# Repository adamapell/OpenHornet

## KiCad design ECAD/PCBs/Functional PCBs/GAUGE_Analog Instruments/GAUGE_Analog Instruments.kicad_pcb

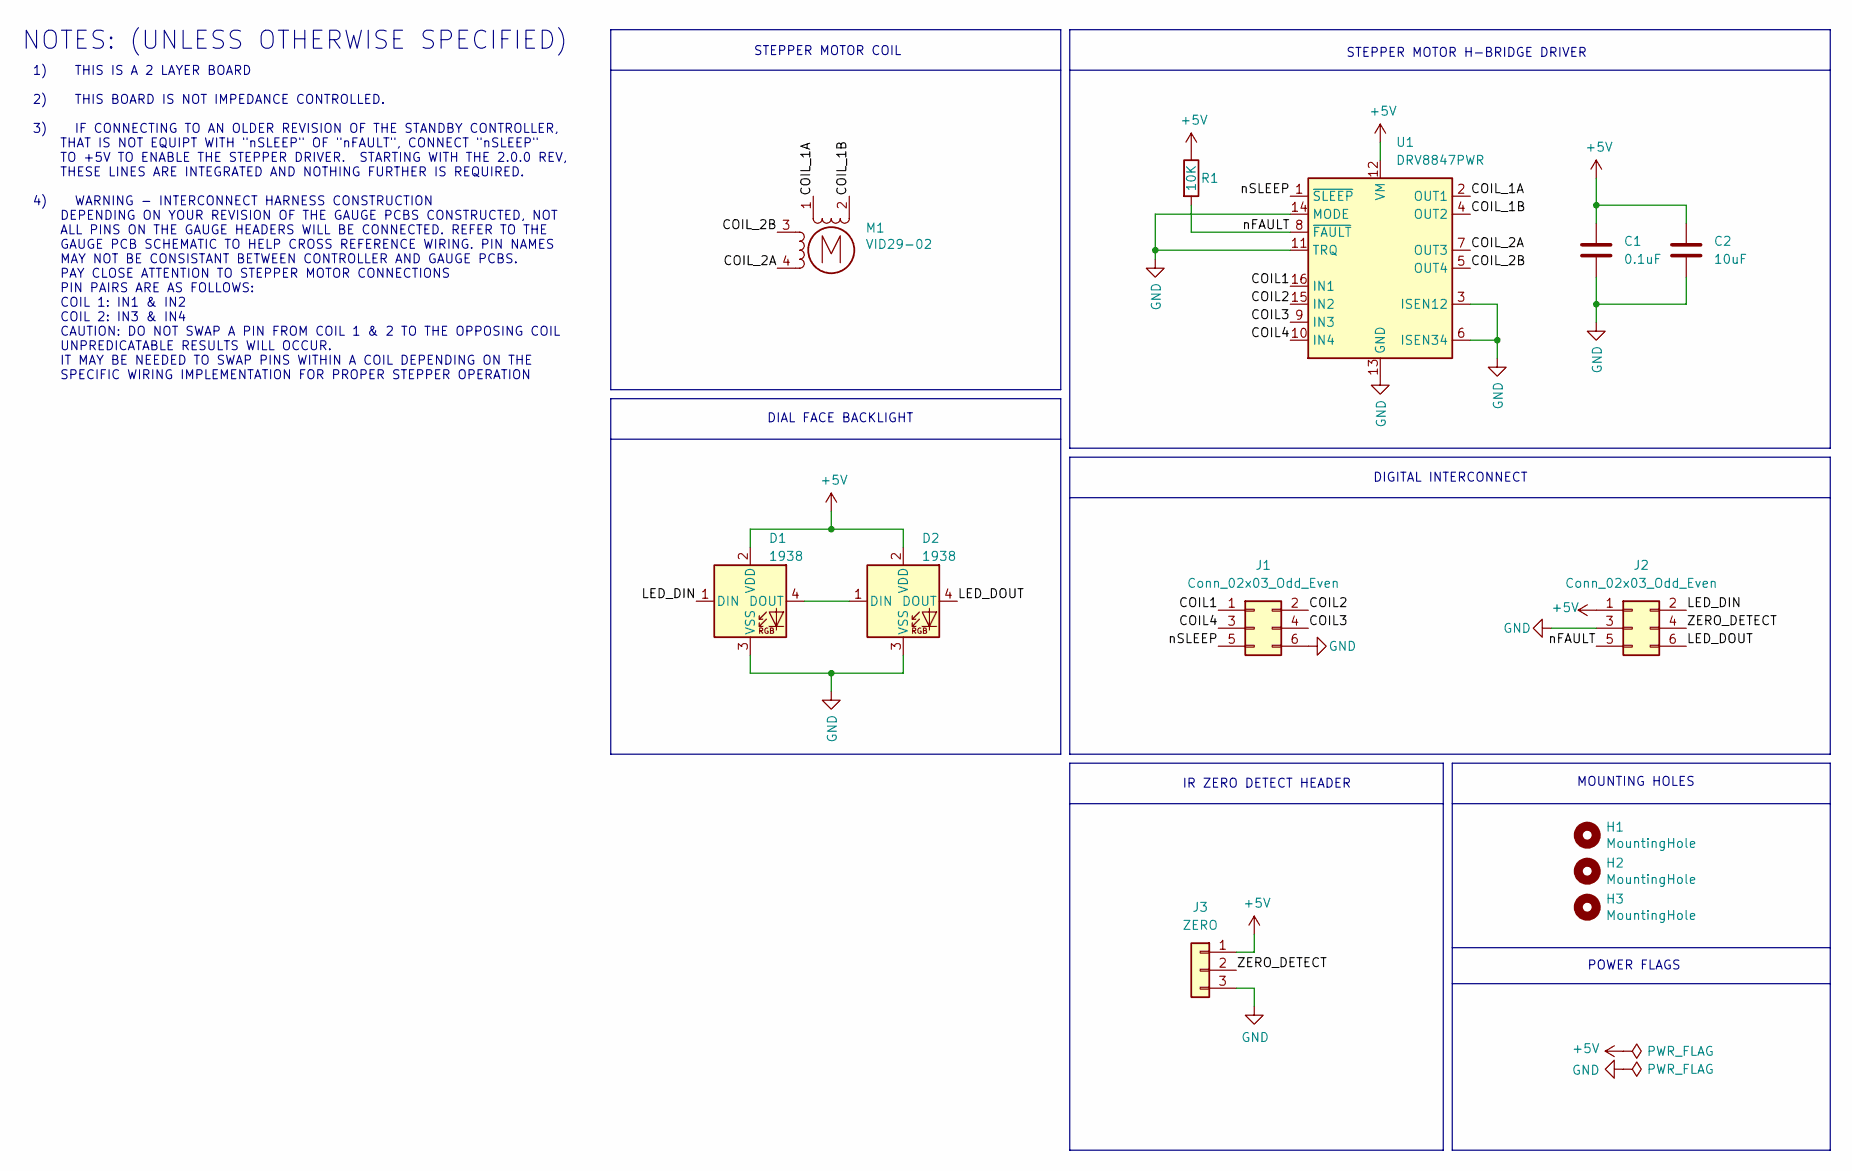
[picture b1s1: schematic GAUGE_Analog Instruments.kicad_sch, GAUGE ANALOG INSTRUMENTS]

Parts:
C1: 0.1uF; C_0603_1608Metric; Manufacturer PN CC0603KRX7R9BB104; LCSC C14663
C2: 10uF; C_0603_1608Metric; Manufacturer PN CL10A106MA8NRNC; LCSC C96446
D1, D2: 1938; LED_D5.0mm-4_RGB
H1, H2, H3: MountingHole; MountingHole_2.5mm
J1, J2: Conn_02x03_Odd_Even; PinHeader_2x03_P2.54mm_Vertical
J3: ZERO; PinHeader_1x03_P2.54mm_Vertical; Manufacturer PN PH1-03-UA
M1: VID29-02
R1: 10K; R_0603_1608Metric; LCSC C25804
U1: DRV8847PWR; TSSOP-16_4.4x5mm_P0.65mm; LCSC C701803

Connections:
+5V: C1.1, C2.1, D1.2 (VDD), D2.2 (VDD), J2.1, J3.1, R1.1, U1.12 (VM)
/COIL1: J1.1, U1.16 (IN1)
/COIL2: J1.2, U1.15 (IN2)
/COIL3: J1.4, U1.9 (IN3)
/COIL4: J1.3, U1.10 (IN4)
/COIL_1A: M1.1, U1.2 (OUT1)
/COIL_1B: M1.2 (-_2), U1.4 (OUT2)
/COIL_2A: M1.4, U1.7 (OUT3)
/COIL_2B: M1.3, U1.5 (OUT4)
/LED_DIN: D1.1 (DIN), J2.2
/LED_DOUT: D2.4 (DOUT), J2.6
/ZERO_DETECT: J2.4, J3.2
/nFAULT: J2.5, R1.2, U1.8 (~FAULT)
/nSLEEP: J1.5, U1.1 (~SLEEP)
GND: C1.2, C2.2, D1.3 (VSS), D2.3 (VSS), J1.6, J2.3, J3.3, U1.3 (ISEN12), U1.6 (ISEN34), U1.11 (TRQ), U1.13 (GND), U1.14 (MODE)
unnamed: D1.4 (DOUT), D2.1 (DIN)

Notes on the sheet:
STEPPER MOTOR COIL
IR ZERO DETECT HEADER
POWER FLAGS
DIAL FACE BACKLIGHT
DIGITAL INTERCONNECT
MOUNTING HOLES
1) THIS IS A 2 LAYER BOARD 2) THIS BOARD IS NOT IMPEDANCE CONTROLLED. 3) IF CONNECTING TO AN OLDER REVISION OF THE STANDBY CONTROLLER, THAT IS NOT EQUIPT WITH "nSLEEP" OF "nFAULT", CONNECT "nSLEEP" TO +5V TO ENABLE THE STEPPER DRIVER. STARTING WITH THE 2.0.0 REV, THESE LINES ARE INTEGRATED AND NOTH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
NOTES: (UNLESS OTHERWISE SPECIFIED)
STEPPER MOTOR H-BRIDGE DRIVER

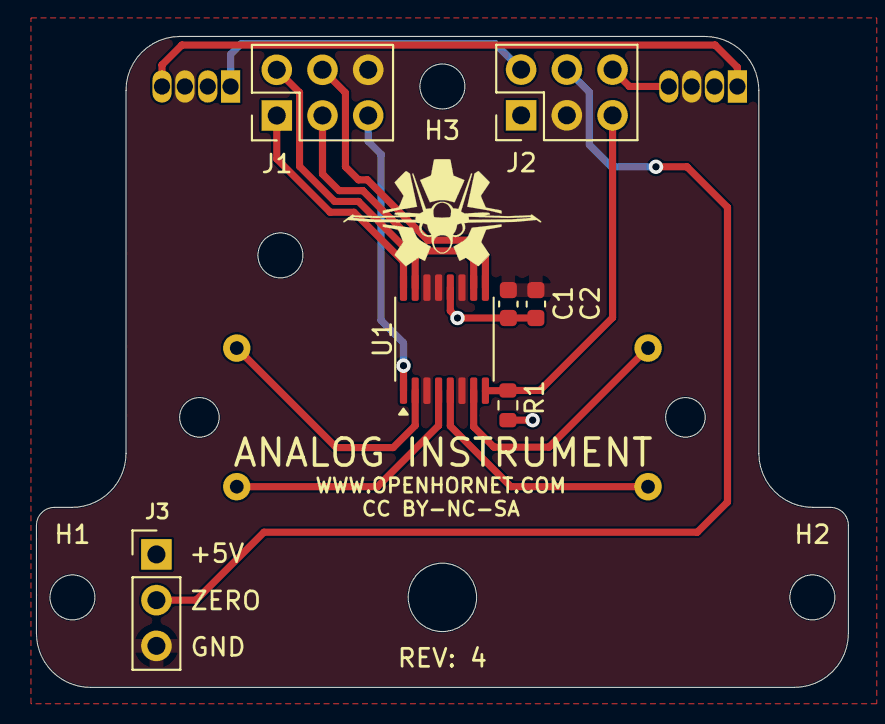
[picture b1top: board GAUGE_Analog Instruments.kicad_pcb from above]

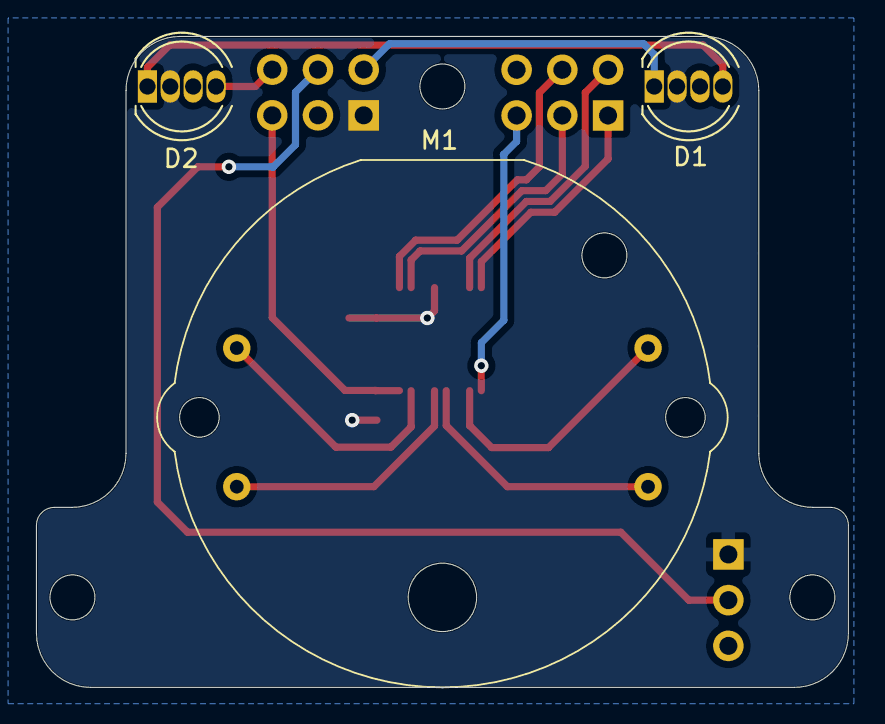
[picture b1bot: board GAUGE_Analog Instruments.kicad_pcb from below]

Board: 2 copper layers, 45.1 x 36.2 mm, 14 parts (2 on the bottom side), 16 nets.

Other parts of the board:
LOGO: LOGO; LOGO_OH_NoText_Small

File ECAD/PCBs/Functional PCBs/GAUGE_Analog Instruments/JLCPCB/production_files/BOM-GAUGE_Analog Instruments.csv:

Comment,Designator,Footprint,LCSC,Quantity
0.1uF,C1,C_0603_1608Metric,C14663,1
10K,R1,R_0603_1608Metric,C25804,1
10uF,C2,C_0603_1608Metric,C96446,1
DRV8847PWR,U1,TSSOP-16_4.4x5mm_P0.65mm,C701803,1
1938,D2,LED_D5.0mm-4_RGB,,1
1938,D1,LED_D5.0mm-4_RGB,,1
VID29-02,M1,VID29-02,,1
MountingHole,H3,MountingHole_2.5mm,,1
MountingHole,H2,MountingHole_2.5mm,,1
MountingHole,H1,MountingHole_2.5mm,,1
Conn_02x03_Odd_Even,J2,PinHeader_2x03_P2.54mm_Vertical,,1
Conn_02x03_Odd_Even,J1,PinHeader_2x03_P2.54mm_Vertical,,1
ZERO,J3,PinHeader_1x03_P2.54mm_Vertical,,1

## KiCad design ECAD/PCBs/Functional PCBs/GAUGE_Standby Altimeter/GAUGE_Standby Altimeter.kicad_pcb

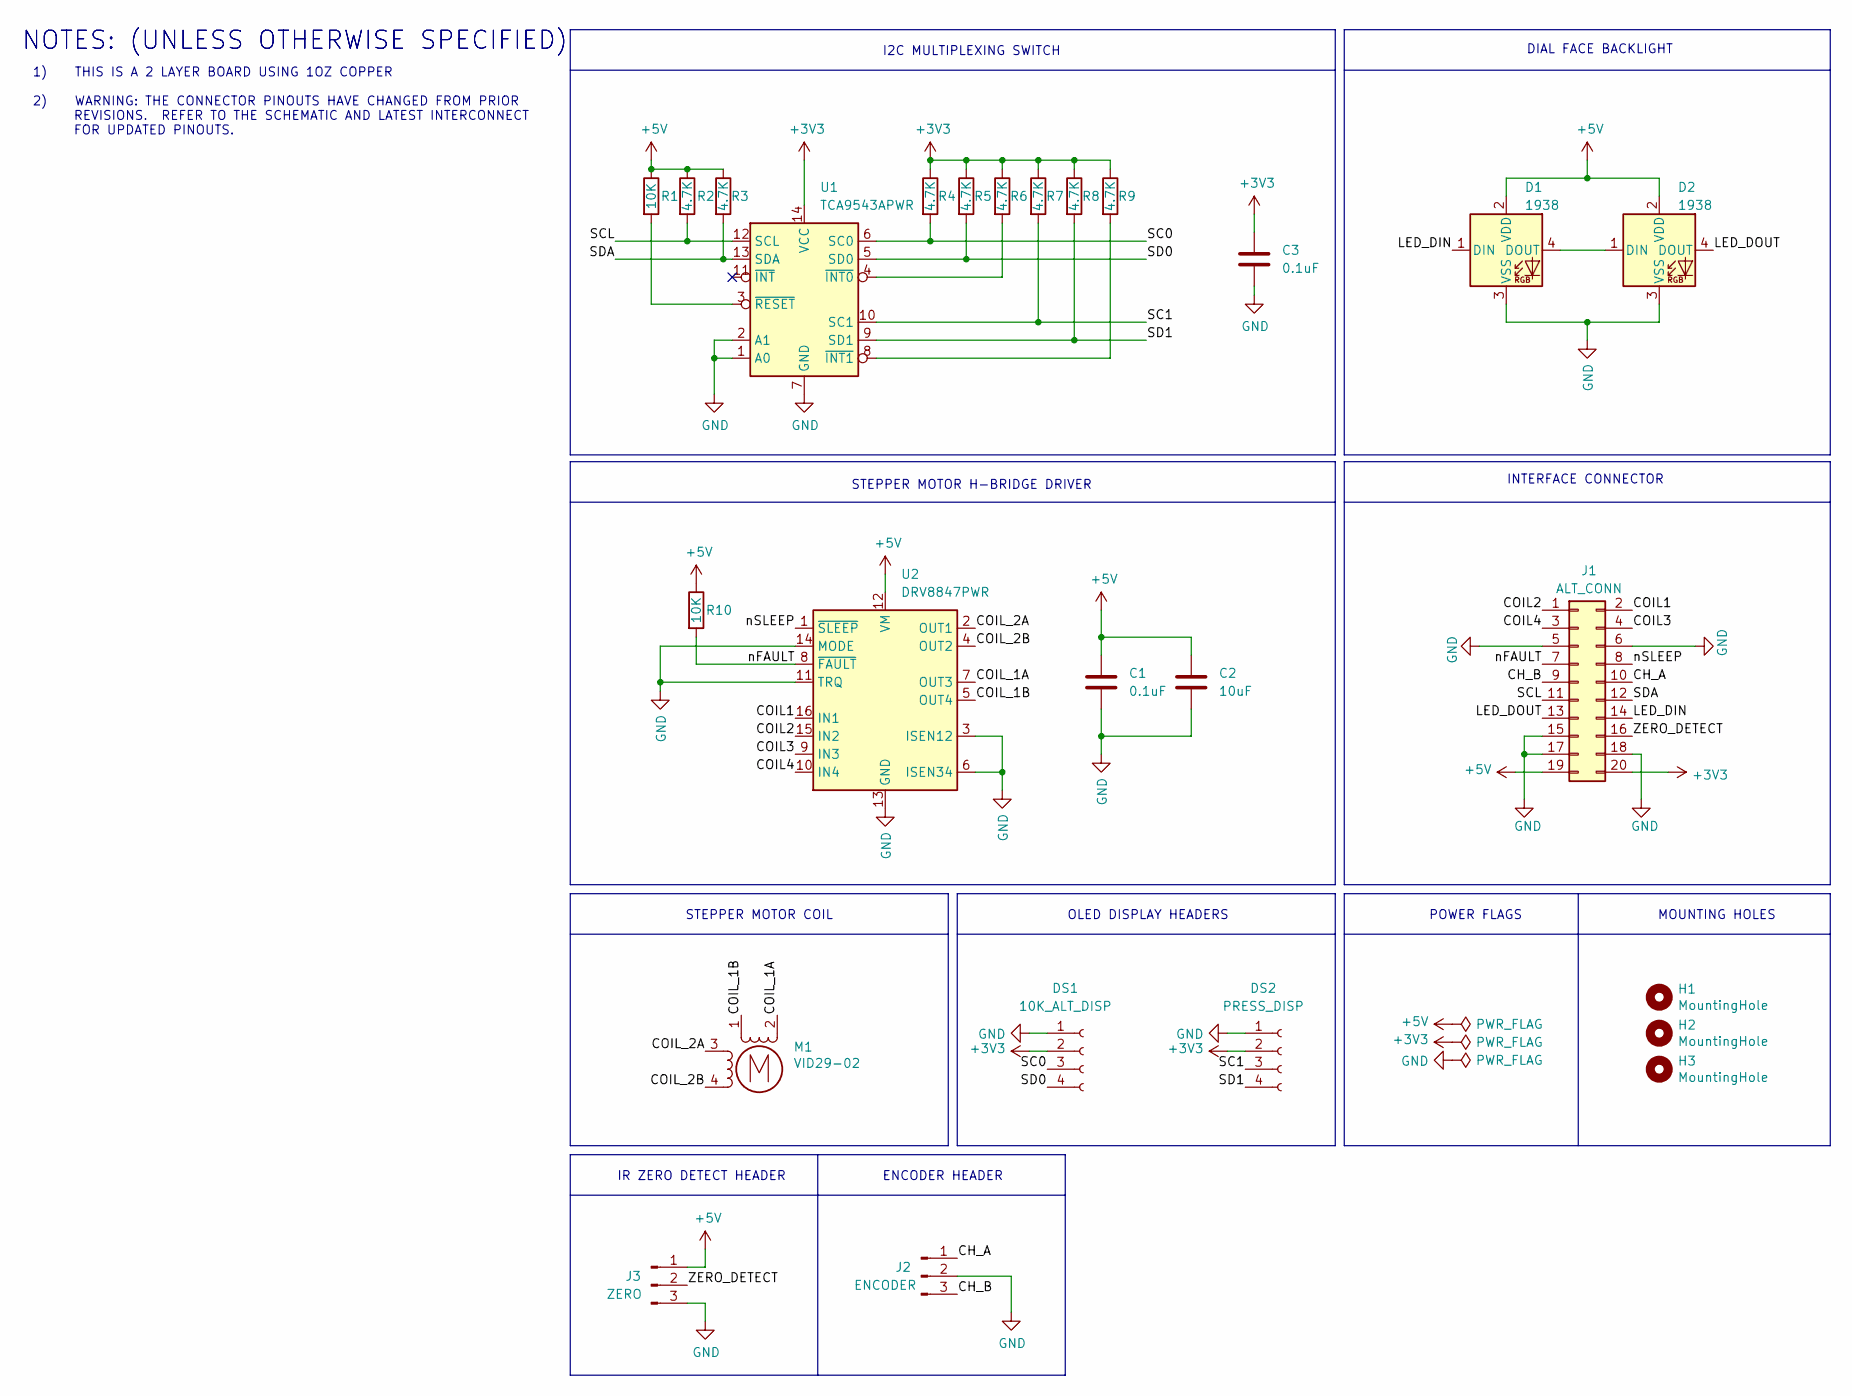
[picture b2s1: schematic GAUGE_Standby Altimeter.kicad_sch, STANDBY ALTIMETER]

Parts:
C1, C3: 0.1uF; C_0603_1608Metric; Manufacturer PN CC0603KRX7R9BB104; LCSC C14663
C2: 10uF; C_0603_1608Metric; Manufacturer PN CL10A106MA8NRNC; LCSC C96446
D1, D2: 1938; LED_D5.0mm-4_RGB
DS1: 10K_ALT_DISP; PinSocket_1x04_P2.54mm_Vertical
DS2: PRESS_DISP; PinSocket_1x04_P2.54mm_Vertical
H1, H2, H3: MountingHole; MountingHole_2.5mm
J1: ALT_CONN; PinHeader_2x10_P2.54mm_Vertical; Manufacturer PN PH2-10-UA
J2: ENCODER; PinHeader_1x03_P2.54mm_Vertical
J3: ZERO; PinHeader_1x03_P2.54mm_Vertical
M1: VID29-02
R1, R10: 10K; R_0603_1608Metric; LCSC C25804
R2, R3, R4, R5, R6, R7, R8, R9: 4.7K; R_0603_1608Metric; Manufacturer PN 0603WAF4701T5E; LCSC C23162
U1: TCA9543APWR; TSSOP-14_4.4x5mm_P0.65mm; LCSC C2653307
U2: DRV8847PWR; TSSOP-16_4.4x5mm_P0.65mm; LCSC C701803

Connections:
+3V3: C3.1, DS1.2, DS2.2, J1.20, R4.1, R5.1, R6.1, R7.1, R8.1, R9.1, U1.14 (VCC)
+5V: C1.1, C2.1, D1.2 (VDD), D2.2 (VDD), J1.19, J3.1, R1.1, R2.1, R3.1, R10.1, U2.12 (VM)
/CH_A: J1.10, J2.1
/CH_B: J1.9, J2.3
/COIL1: J1.2, U2.16 (IN1)
/COIL2: J1.1, U2.15 (IN2)
/COIL3: J1.4, U2.9 (IN3)
/COIL4: J1.3, U2.10 (IN4)
/COIL_1A: M1.2 (-_2), U2.7 (OUT3)
/COIL_1B: M1.1, U2.5 (OUT4)
/COIL_2A: M1.3, U2.2 (OUT1)
/COIL_2B: M1.4, U2.4 (OUT2)
/LED_DIN: D1.1 (DIN), J1.14
/LED_DOUT: D2.4 (DOUT), J1.13
/SC0: DS1.3, R4.2, U1.6 (SC0)
/SC1: DS2.3, R7.2, U1.10 (SC1)
/SCL: J1.11, R2.2, U1.12 (SCL)
/SD0: DS1.4, R5.2, U1.5 (SD0)
/SD1: DS2.4, R8.2, U1.9 (SD1)
/SDA: J1.12, R3.2, U1.13 (SDA)
/ZERO_DETECT: J1.16, J3.2
/nFAULT: J1.7, R10.2, U2.8 (~FAULT)
/nSLEEP: J1.8, U2.1 (~SLEEP)
GND: C1.2, C2.2, C3.2, D1.3 (VSS), D2.3 (VSS), DS1.1, DS2.1, J1.5, J1.6, J1.15, J1.17, J1.18, J2.2, J3.3, U1.1 (A0), U1.2 (A1), U1.7 (GND), U2.3 (ISEN12), U2.6 (ISEN34), U2.11 (TRQ), U2.13 (GND), U2.14 (MODE)
unnamed: D1.4 (DOUT), D2.1 (DIN)
unnamed: R6.2, U1.4 (~INT0)
unnamed: R9.2, U1.8 (~INT1)
unnamed: R1.2, U1.3 (~RESET)

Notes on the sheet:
NOTES: (UNLESS OTHERWISE SPECIFIED)
1) THIS IS A 2 LAYER BOARD USING 1OZ COPPER 2) WARNING: THE CONNECTOR PINOUTS HAVE CHANGED FROM PRIOR REVISIONS. REFER TO THE SCHEMATIC AND LATEST INTERCONNECT FOR UPDATED PINOUTS.
DIAL FACE BACKLIGHT
ENCODER HEADER
STEPPER MOTOR COIL
I2C MULTIPLEXING SWITCH
INTERFACE CONNECTOR
POWER FLAGS
MOUNTING HOLES
IR ZERO DETECT HEADER
STEPPER MOTOR H-BRIDGE DRIVER
OLED DISPLAY HEADERS

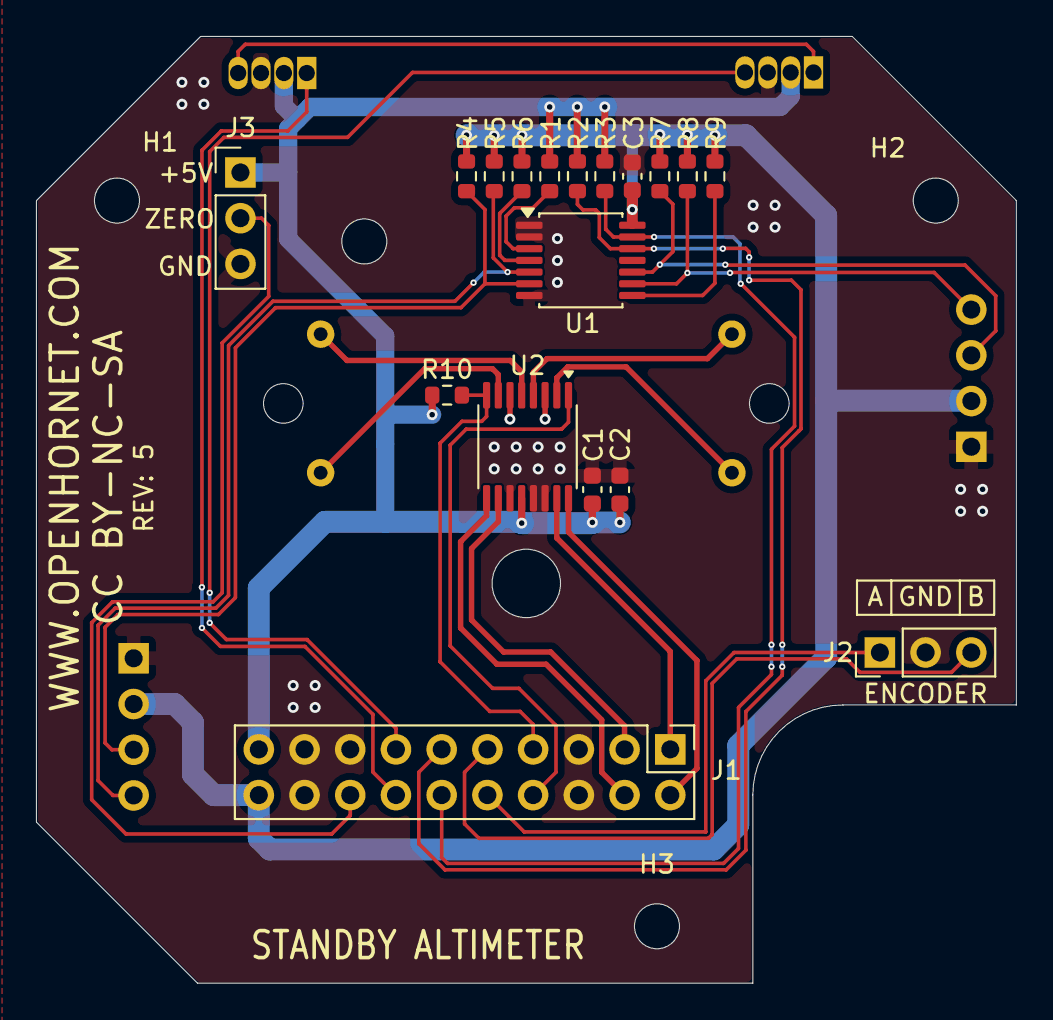
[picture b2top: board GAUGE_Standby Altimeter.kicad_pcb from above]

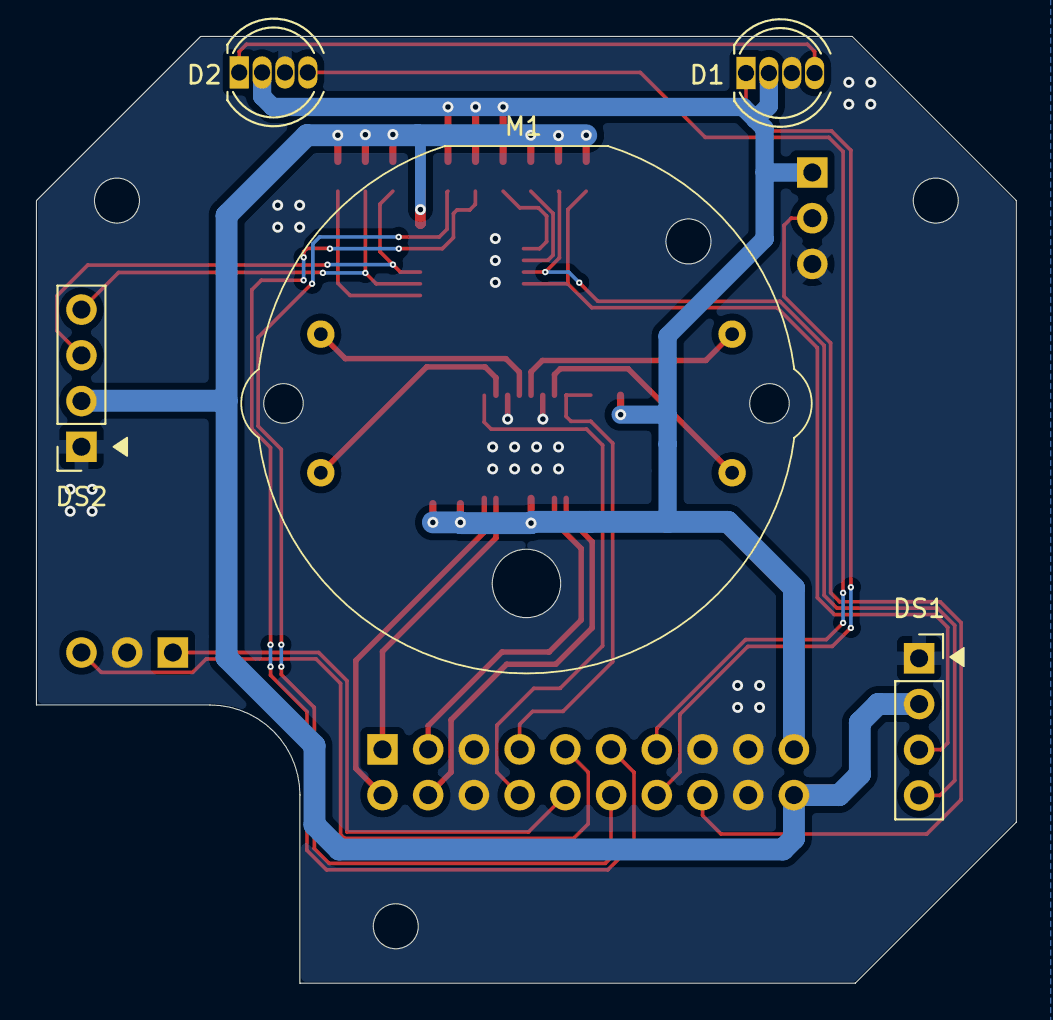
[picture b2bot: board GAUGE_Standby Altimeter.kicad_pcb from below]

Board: 2 copper layers, 54.4 x 52.6 mm, 26 parts (4 on the bottom side), 28 nets.

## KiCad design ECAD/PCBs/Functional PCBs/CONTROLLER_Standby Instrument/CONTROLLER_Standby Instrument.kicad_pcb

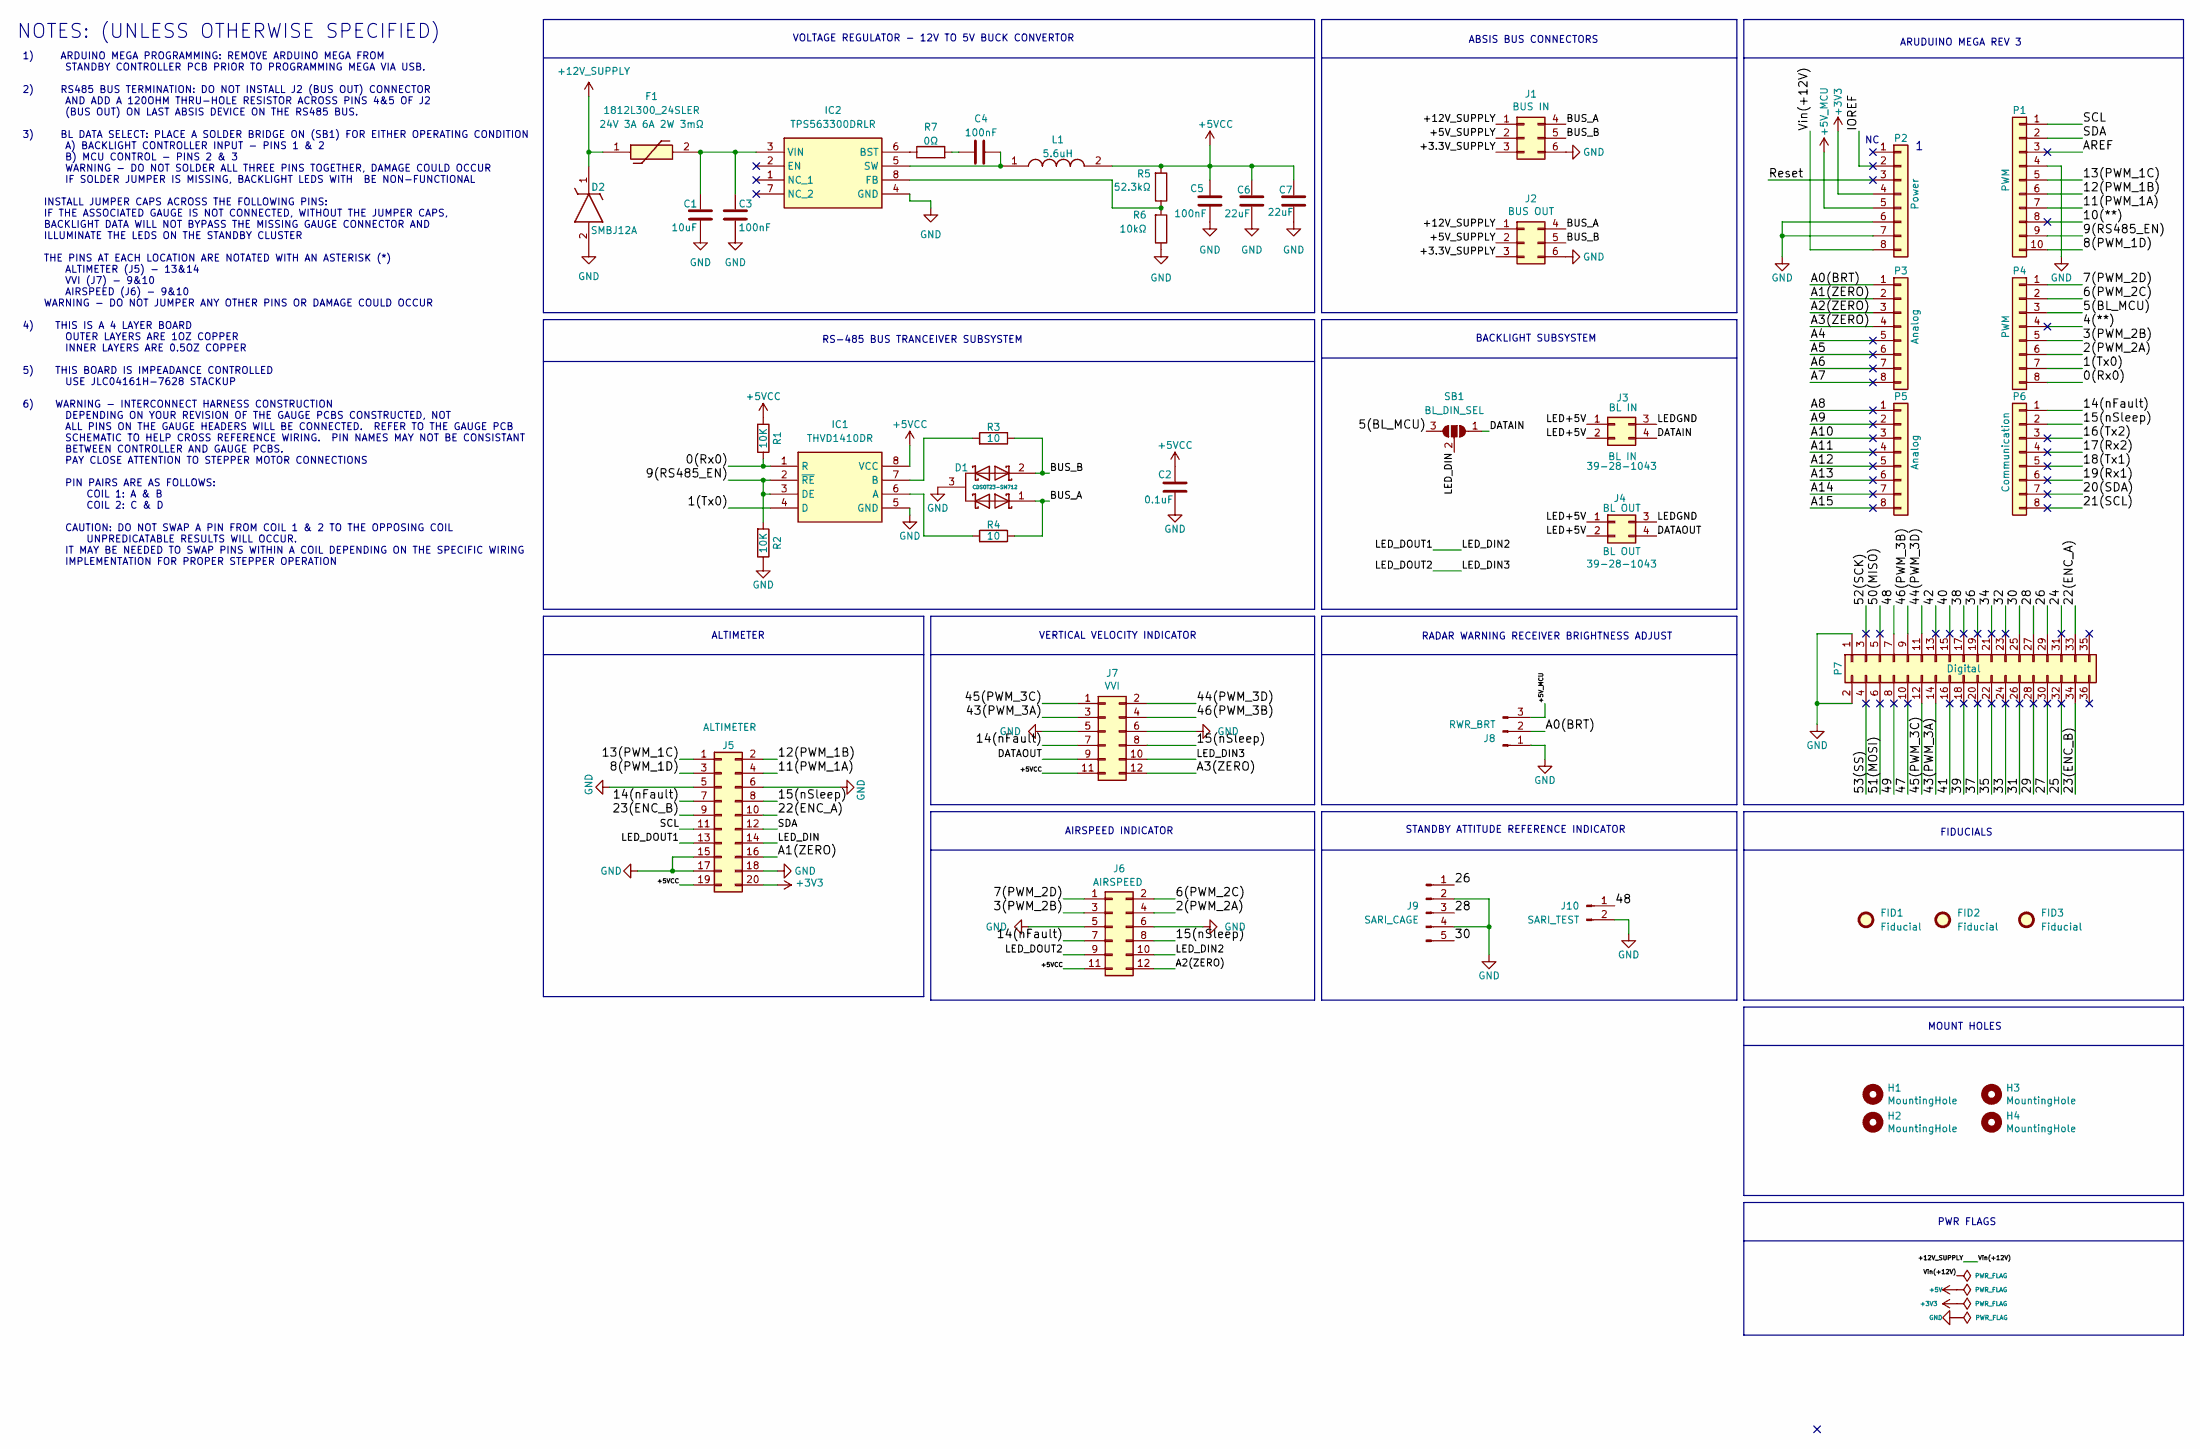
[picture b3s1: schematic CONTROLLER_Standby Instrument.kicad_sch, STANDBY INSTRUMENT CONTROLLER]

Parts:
C1: 10uF; C_0603_1608Metric; Manufacturer PN CL10A106MA8NRNC; LCSC C96446
C2: 0.1uF; C_0603_1608Metric; Manufacturer PN CC0603KRX7R9BB104; LCSC C14663
C3, C4: 100nF; C_0402_1005Metric; Manufacturer PN CL05B104KB54PNC; LCSC C307331
C5: 100nF; C_0805_2012Metric; Manufacturer PN CC0805KRX7R9BB104; LCSC C49678
C6, C7: 22uF; C_0805_2012Metric; Manufacturer PN CL21A226MAQNNNE; LCSC C45783
D1: CDSOT23-SM712; Manufacturer_Part_Number CDSOT23-SM712; Mouser Part Number 652-CDSOT23-SM712
D2: SMBJ12A; D_SMB; Manufacturer PN SMBJ12A; LCSC C151251
F1: 1812L300_24SLER; Fuse_1812_4532Metric; Manufacturer PN 1812L300/24SLER; LCSC C1512049
FID1, FID2, FID3: Fiducial; Fiducial_1mm_Mask2mm
H1, H2, H3, H4: MountingHole; MountingHole_2.5mm
IC1: THVD1410DR; Manufacturer_Part_Number THVD1410DR; Mouser Part Number 595-THVD1410DR
IC2: TPS563300DRLR; SOT-583-8; Manufacturer PN TPS563300DRLR; LCSC C5219249
J1: BUS IN; Molex_Mini-Fit_Jr_5569-06A1_2x03_P4.20mm_Horizontal
J2: BUS OUT; Molex_Mini-Fit_Jr_5569-06A1_2x03_P4.20mm_Horizontal
J3: BL IN; Molex_Mini-Fit_Jr_5566-04A_2x02_P4.20mm_Vertical; Manufacturer PN 39-28-1043; LCSC C293502
J4: BL OUT; Molex_Mini-Fit_Jr_5566-04A_2x02_P4.20mm_Vertical; Manufacturer PN 39-28-1043; LCSC C293502
J5: ALTIMETER; PinHeader_2x10_P2.54mm_Vertical; Manufacturer PN PH2-10-UA
J6: AIRSPEED; PinHeader_2x06_P2.54mm_Vertical; Manufacturer PN B-2100S12P-B110; LCSC PH2-6-UA
J7: VVI; PinHeader_2x06_P2.54mm_Vertical
J8: RWR_BRT; PinHeader_1x03_P2.54mm_Vertical
J9: SARI_CAGE; PinHeader_1x05_P2.54mm_Vertical
J10: SARI_TEST; PinHeader_1x02_P2.54mm_Vertical
L1: 5.6uH; L_Bourns_SRP6060FA; Manufacturer PN SRP6540-5R6M; LCSC C2041376
P1: PWM; PinHeader_1x10_P2.54mm_Vertical
P2: Power; PinHeader_1x08_P2.54mm_Vertical
P3, P5: Analog; PinHeader_1x08_P2.54mm_Vertical
P4: PWM; PinHeader_1x08_P2.54mm_Vertical
P6: Communication; PinHeader_1x08_P2.54mm_Vertical
P7: Digital; PinHeader_2x18_P2.54mm_Vertical
R1, R2: 10K; R_0603_1608Metric_Pad0.98x0.95mm_HandSolder; LCSC C25804
R3, R4: 10; R_0603_1608Metric_Pad0.98x0.95mm_HandSolder; LCSC C844519
R5: 52.3kΩ; R_0402_1005Metric; Manufacturer PN 0402WGF5232TCE; LCSC C26982
R6: 10kΩ; R_0402_1005Metric; Manufacturer PN 0402WGF1002TCE; LCSC C25744
R7: 0Ω; R_0402_1005Metric; Manufacture PN 0402WGF0000TCE; LCSC C17168
SB1: BL_DIN_SEL; SolderJumper-3_P1.3mm_Open_RoundedPad1.0x1.5mm

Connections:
+3V3: J5.20, P2.4
+5VCC: C2.2, C5.1, C6.1, C7.1, IC1.8 (VCC), J5.19, J6.11, J7.11, L1.2, R1.2, R5.2
+5V_MCU: J8.3, P2.5
+12V_SUPPLY: D2.1 (K), F1.1, J1.1, J2.1, P2.8
/0(Rx0): IC1.1 (R), P4.8, R1.1
/1(Tx0): IC1.4 (D), P4.7
/2(PWM_2A): J6.4, P4.6
/3(PWM_2B): J6.3, P4.5
/4(**): P4.4
/5(BL_MCU): P4.3, SB1.3 (B)
/6(PWM_2C): J6.2, P4.2
/7(PWM_2D): J6.1, P4.1
/8(PWM_1D): J5.3, P1.10
/9(RS485_EN): IC1.2 (~RE), IC1.3 (DE), P1.9, R2.2
/10(**): P1.8
/11(PWM_1A): J5.4, P1.7
/12(PWM_1B): J5.2, P1.6
/13(PWM_1C): J5.1, P1.5
/14(nFault): J5.7, J6.7, J7.7, P6.1
/15(nSleep): J5.8, J6.8, J7.8, P6.2
/16(Tx2): P6.3
/17(Rx2): P6.4
/18(Tx1): P6.5
/19(Rx1): P6.6
/20(SDA): P6.7
/21(SCL): P6.8
/22(ENC_A): J5.10, P7.33
/23(ENC_B): J5.9, P7.34
/24: P7.31
/25: P7.32
/26: J9.1, P7.29
/27: P7.30
/28: J9.3, P7.27
/29: P7.28
/30: J9.5, P7.25
/31: P7.26
/32: P7.23
/33: P7.24
/34: P7.21
/35: P7.22
/36: P7.19
/37: P7.20
/38: P7.17
/39: P7.18
/40: P7.15
/41: P7.16
/42: P7.13
/43(PWM_3A): J7.3, P7.14
/44(PWM_3D): J7.2, P7.11
/45(PWM_3C): J7.1, P7.12
/46(PWM_3B): J7.4, P7.9
/47: P7.10
/48: J10.1, P7.7
/49: P7.8
/50(MISO): P7.5
/51(MOSI): P7.6
/52(SCK): P7.3
/53(SS): P7.4
/+3.3V_SUPPLY: J1.3, J2.3
/+5V_SUPPLY: J1.2, J2.2
/A0(BRT): J8.2, P3.1
/A1(ZERO): J5.16, P3.2
/A2(ZERO): J6.12, P3.3
/A3(ZERO): J7.12, P3.4
/A4: P3.5
/A5: P3.6
/A6: P3.7
/A7: P3.8
/A8: P5.1
/A9: P5.2
/A10: P5.3
/A11: P5.4
/A12: P5.5
/A13: P5.6
/A14: P5.7
/A15: P5.8
/AREF: P1.3
/BUS_A: D1.1, J1.4, J2.4, R4.2
/BUS_B: D1.2, J1.5, J2.5, R3.2
/DATAIN: J3.4, SB1.1 (A)
/DATAOUT: J4.4, J7.9
/IOREF: P2.2
/LED+5V: J3.1, J3.2 (Pin_3), J4.1, J4.2 (Pin_3)
/LEDGND: J3.3 (Pin_2), J4.3 (Pin_2)
/LED_DIN: J5.14, SB1.2 (C)
/LED_DIN2: J5.13, J6.10
/LED_DIN3: J6.9, J7.10
/Reset: P2.3
/SCL: J5.11, P1.1
/SDA: J5.12, P1.2
GND: C1.1, C2.1, C3.1, C5.2, C6.2, C7.2, D1.3, D2.2 (A), IC1.5 (GND), IC2.4 (GND), J1.6, J2.6, J5.5, J5.6, J5.15, J5.17, J5.18, J6.5, J6.6, J7.5, J7.6, J8.1, J9.2, J9.4, J10.2, P1.4, P2.6, P2.7, P7.1, P7.2, R2.1, R6.1
unnamed: C4.2, R7.2
unnamed: IC1.6 (A), R4.1
unnamed: IC1.7 (B), R3.1
unnamed: IC2.6 (BST), R7.1
unnamed: IC2.8 (FB), R5.1, R6.2
unnamed: C4.1, IC2.5 (SW), L1.1
unnamed: C1.2, C3.2, F1.2, IC2.3 (VIN)

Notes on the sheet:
VOLTAGE REGULATOR - 12V TO 5V BUCK CONVERTOR
ARUDUINO MEGA REV 3
FIDUCIALS
STANDBY ATTITUDE REFERENCE INDICATOR
PWR FLAGS
RADAR WARNING RECEIVER BRIGHTNESS ADJUST
1) ARDUINO MEGA PROGRAMMING: REMOVE ARDUINO MEGA FROM STANDBY CONTROLLER PCB PRIOR TO PROGRAMMING MEGA VIA USB. 2) RS485 BUS TERMINATION: DO NOT INSTALL J2 (BUS OUT) CONNECTOR AND ADD A 120OHM THRU-HOLE RESISTOR ACROSS PINS 4&5 OF J2 (BUS OUT) ON LAST ABSIS DEVICE ON THE RS485 BUS. 3) BL DATA SELEC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
AIRSPEED INDICATOR
NOTES: (UNLESS OTHERWISE SPECIFIED)
ABSIS BUS CONNECTORS
ALTIMETER
VERTICAL VELOCITY INDICATOR
RS-485 BUS TRANCEIVER SUBSYSTEM
MOUNT HOLES
BACKLIGHT SUBSYSTEM

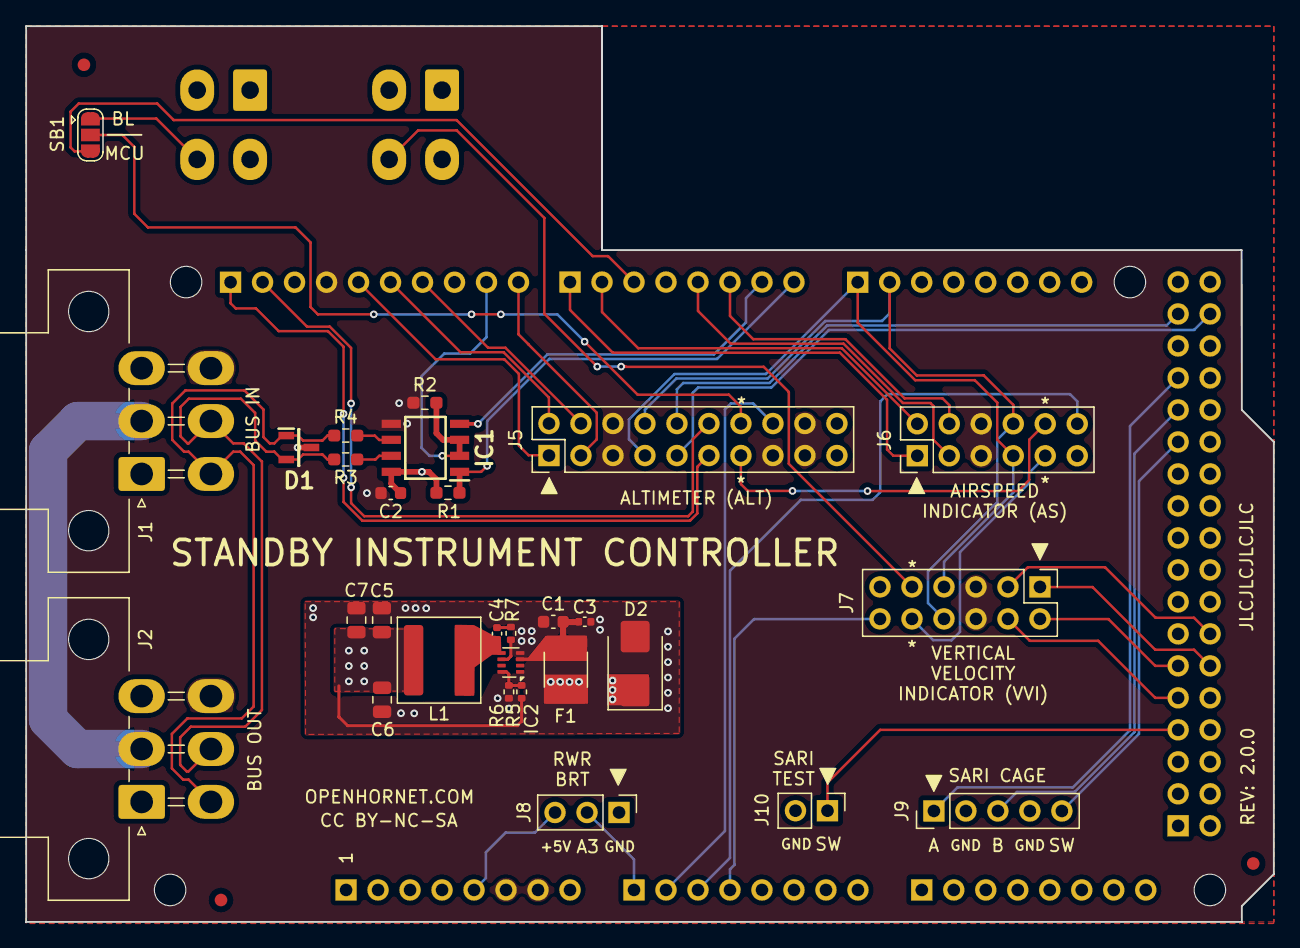
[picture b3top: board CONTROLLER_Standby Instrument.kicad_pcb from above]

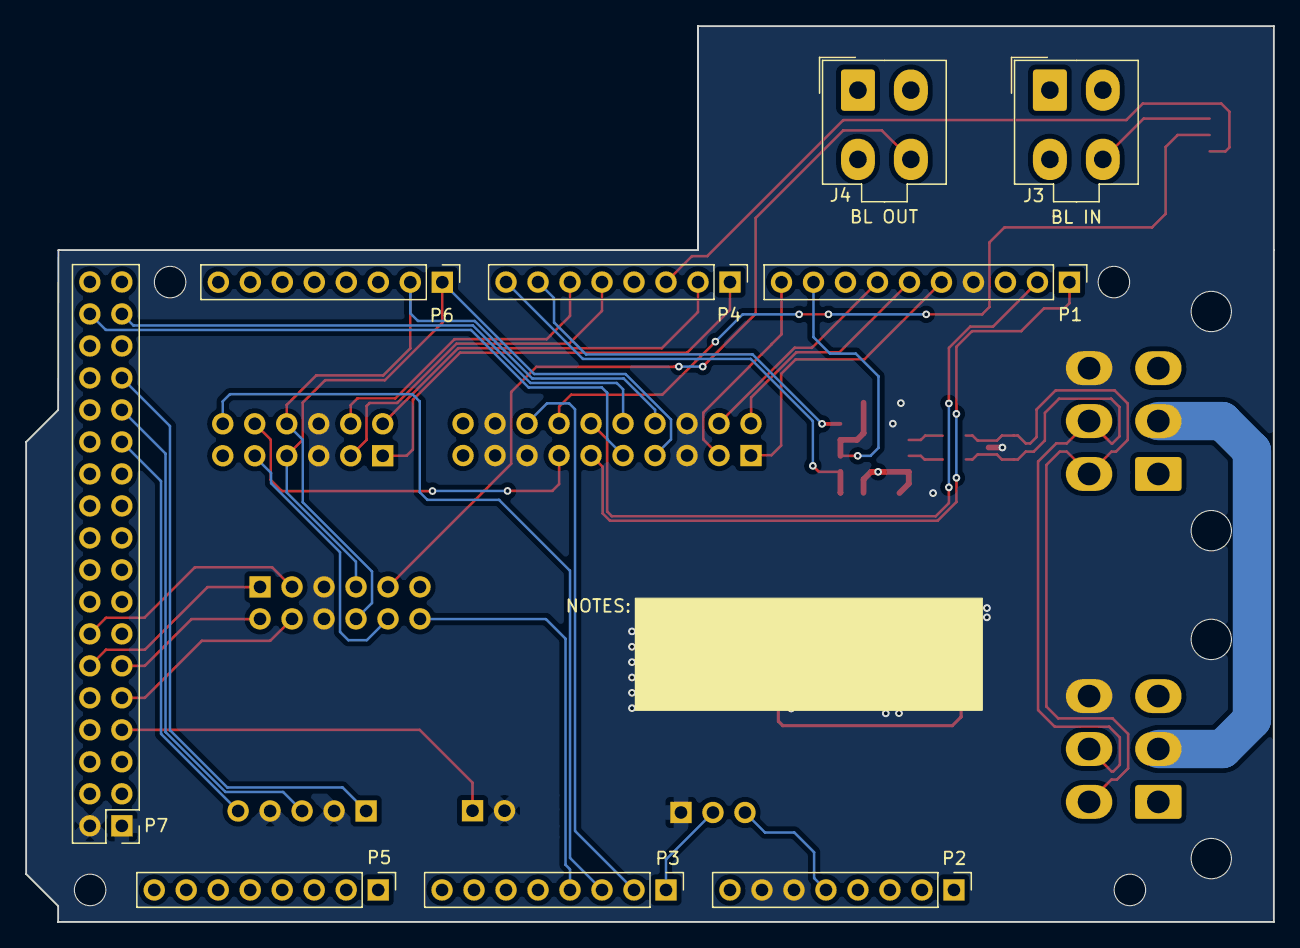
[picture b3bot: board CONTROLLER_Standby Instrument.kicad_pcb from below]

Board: 4 copper layers, 99.1 x 71.1 mm, 45 parts (9 on the bottom side), 53 nets.

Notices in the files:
ECAD/PCBs/ABSIS/ABSIS_ATX Power Supply Unit/ABSIS_ATX Power Supply Unit.kicad_pcb:
License:  CC BY-NC-SA
CC-BY-NC-SA
ECAD/PCBs/ABSIS/ABSIS_Backlight Controller/ABSIS_Backlight Controller.kicad_pcb:
OPENHORNET.COM - CC BY-NC-SA
